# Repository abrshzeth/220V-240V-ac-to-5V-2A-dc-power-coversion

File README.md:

# AC/DC Flyback Power Converter — 5V / 2A

> **Industrial-grade isolated flyback converter** stepping down Ethiopian mains (220–240V AC / 50Hz) to a regulated 5V DC / 2A output. Designed as an internship project for **DAF Tech Social ICT Solutions**, June 2026.

---

## ⚠️ Safety Warning

This project operates directly from **220–240V AC mains voltage**. Incorrect assembly or handling can result in **electric shock, fire, or death**. Do not build or test this circuit unless you are qualified to work with mains-voltage electronics. Always disconnect from mains before touching the board.

---

## Project Overview

This repository contains the complete KiCad schematic, PCB layout, and bill of materials for a **10W isolated flyback AC/DC power converter**. The design converts Ethiopian standard mains voltage to a stable, regulated 5V DC output suitable for charging mobile phones and powering low-voltage electronics.

The design was built entirely from scratch during a 2-week internship period, covering component selection, schematic capture, PCB layout, and documentation.

---

## Specifications

| Parameter | Value |
|---|---|
| Input voltage | 220 – 240V AC |
| Input frequency | 50 Hz |
| Output voltage | 5V DC (regulated ±1%) |
| Output current | 2A maximum |
| Output power | 10W |
| Efficiency | ~82% |
| Isolation voltage | 3000V AC (IEC 62368-1) |
| Switching frequency | 65 kHz |
| Output ripple | < 50mVpp |
| PCB layers | 2 (double-sided) |
| PCB creepage | 6mm minimum (HV to LV) |
| Operating temperature | −10°C to +70°C |

---

## Topology

**Isolated flyback converter** using the STMicroelectronics VIPer22AS PWM controller IC, which integrates the power MOSFET and control logic in a single SO-8 package. Feedback regulation is achieved through a TL431 shunt regulator and PC817C optocoupler maintaining full galvanic isolation between primary (mains) and secondary (output) sides.

## License

This project is released for educational purposes. Use at your own risk. The authors accept no liability for damage, injury, or death resulting from the construction or use of this circuit.

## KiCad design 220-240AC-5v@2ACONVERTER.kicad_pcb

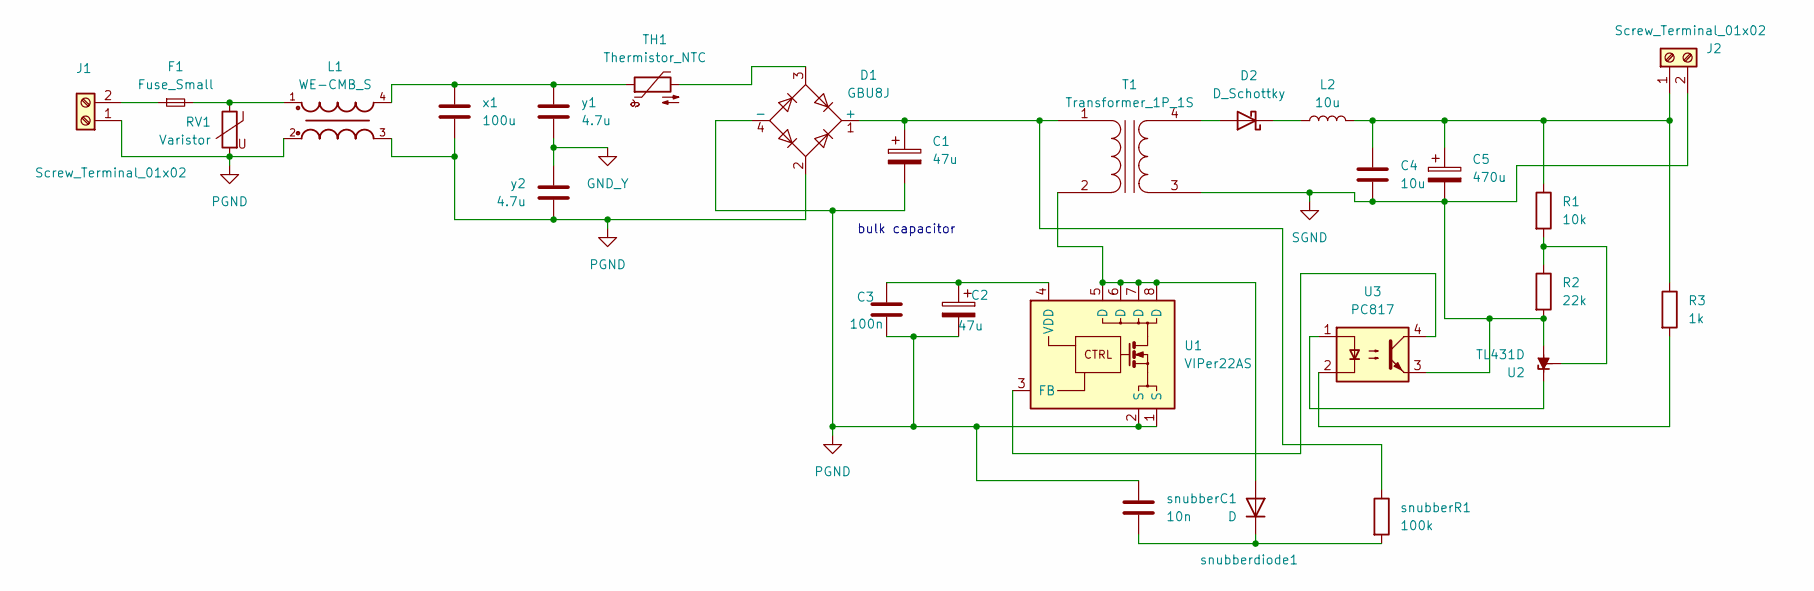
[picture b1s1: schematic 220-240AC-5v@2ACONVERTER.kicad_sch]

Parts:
C1: 47u; CP_Radial_D18.0mm_P7.50mm
C2: 47u; CP_Radial_D6.3mm_P2.50mm
C3: 100n; C_Disc_D5.0mm_W2.5mm_P2.50mm
C4: 10u; C_Disc_D5.0mm_W2.5mm_P2.50mm
C5: 470u; CP_Radial_D10.0mm_P5.00mm
D1: GBU8J; Diode_Bridge_Vishay_GBU
D2: D_Schottky; D_DO-201AD_P12.70mm_Horizontal
F1: Fuse_Small; Fuseholder_Clip-5x20mm_Littelfuse_521_Lateral_P17.00x5.00mm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
J1, J2: Screw_Terminal_01x02; TerminalBlock_bornier-2_P5.08mm
L1: WE-CMB_S
L2: 10u; L_6.3x6.3_H3
R1: 10k; R_Axial_DIN0204_L3.6mm_D1.6mm_P5.08mm_Vertical
R2: 22k; R_Axial_DIN0204_L3.6mm_D1.6mm_P5.08mm_Vertical
R3: 1k; R_Axial_DIN0204_L3.6mm_D1.6mm_P5.08mm_Vertical
RV1: Varistor; RV_Disc_D7mm_W3.4mm_P5mm
T1: Transformer_1P_1S; Transformer_Wuerth_750315371
TH1: Thermistor_NTC; RV_Disc_D21.5mm_W6.1mm_P7.5mm
U1: VIPer22AS; SOIC-8_3.9x4.9mm_P1.27mm
U2: TL431D; SOIC-8_3.9x4.9mm_P1.27mm
U3: PC817; DIP-4_W7.62mm
snubberC1: 10n; C_Disc_D5.0mm_W2.5mm_P2.50mm
snubberR1: 100k; R_Axial_DIN0411_L9.9mm_D3.6mm_P20.32mm_Horizontal
snubberdiode1: D; D_DO-41_SOD81_P7.62mm_Horizontal
x1: 100u; C_Rect_L18.0mm_W5.0mm_P15.00mm_FKS3_FKP3
y1, y2: 4.7u; C_Disc_D7.5mm_W2.5mm_P5.00mm

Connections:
GND_Y: y1.2, y2.1
unnamed: C1.1, D1.1 (+), T1.1 (AA), snubberR1.1
unnamed: D1.3, TH1.2
unnamed: D2.2 (A), T1.4 (SB)
unnamed: D2.1 (K), L2.1
unnamed: F1.2, L1.1, RV1.1
unnamed: F1.1, J1.2
unnamed: C4.1, C5.1, J2.1, L2.2, R1.1, R3.1
unnamed: L1.4, TH1.1, x1.1, y1.1
unnamed: R3.2, U3.2
unnamed: T1.2 (AB), U1.5 (D), U1.6 (D), U1.7 (D), U1.8 (D), snubberdiode1.2 (A)
unnamed: U1.3 (FB), U3.4
unnamed: C2.1, C3.1, U1.4 (VDD)
unnamed: U2.1 (K), U3.1
unnamed: R1.2, R2.1, U2.8 (REF)
unnamed: snubberC1.2, snubberR1.2, snubberdiode1.1 (K)
PGND: C1.2, C2.2, C3.2, D1.2, D1.4 (-), J1.1, L1.2, L1.3, RV1.2, U1.1 (S), U1.2 (S), snubberC1.1, x1.2, y2.2
SGND: C4.2, C5.2, J2.2, R2.2, T1.3 (SA), U2.2 (A), U2.3 (A), U2.6 (A), U2.7 (A), U3.3

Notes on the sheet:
bulk capacitor

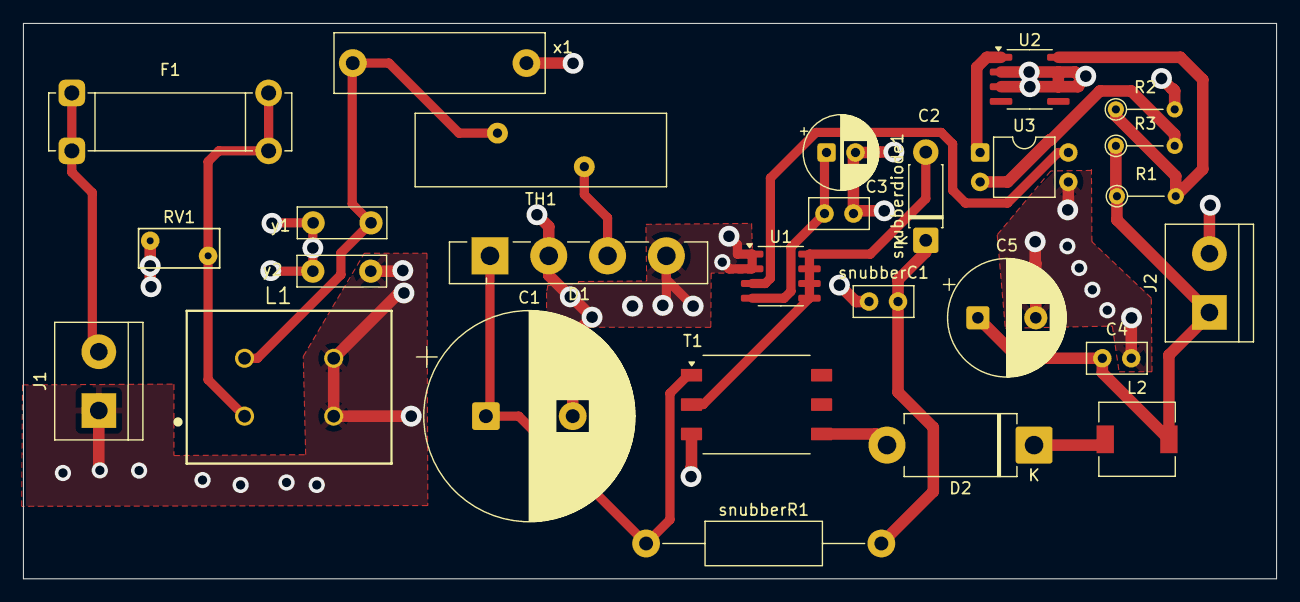
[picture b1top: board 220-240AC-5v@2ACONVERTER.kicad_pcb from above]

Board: 2 copper layers, 108.3 x 48.0 mm, 27 parts (0 on the bottom side), 18 nets.
